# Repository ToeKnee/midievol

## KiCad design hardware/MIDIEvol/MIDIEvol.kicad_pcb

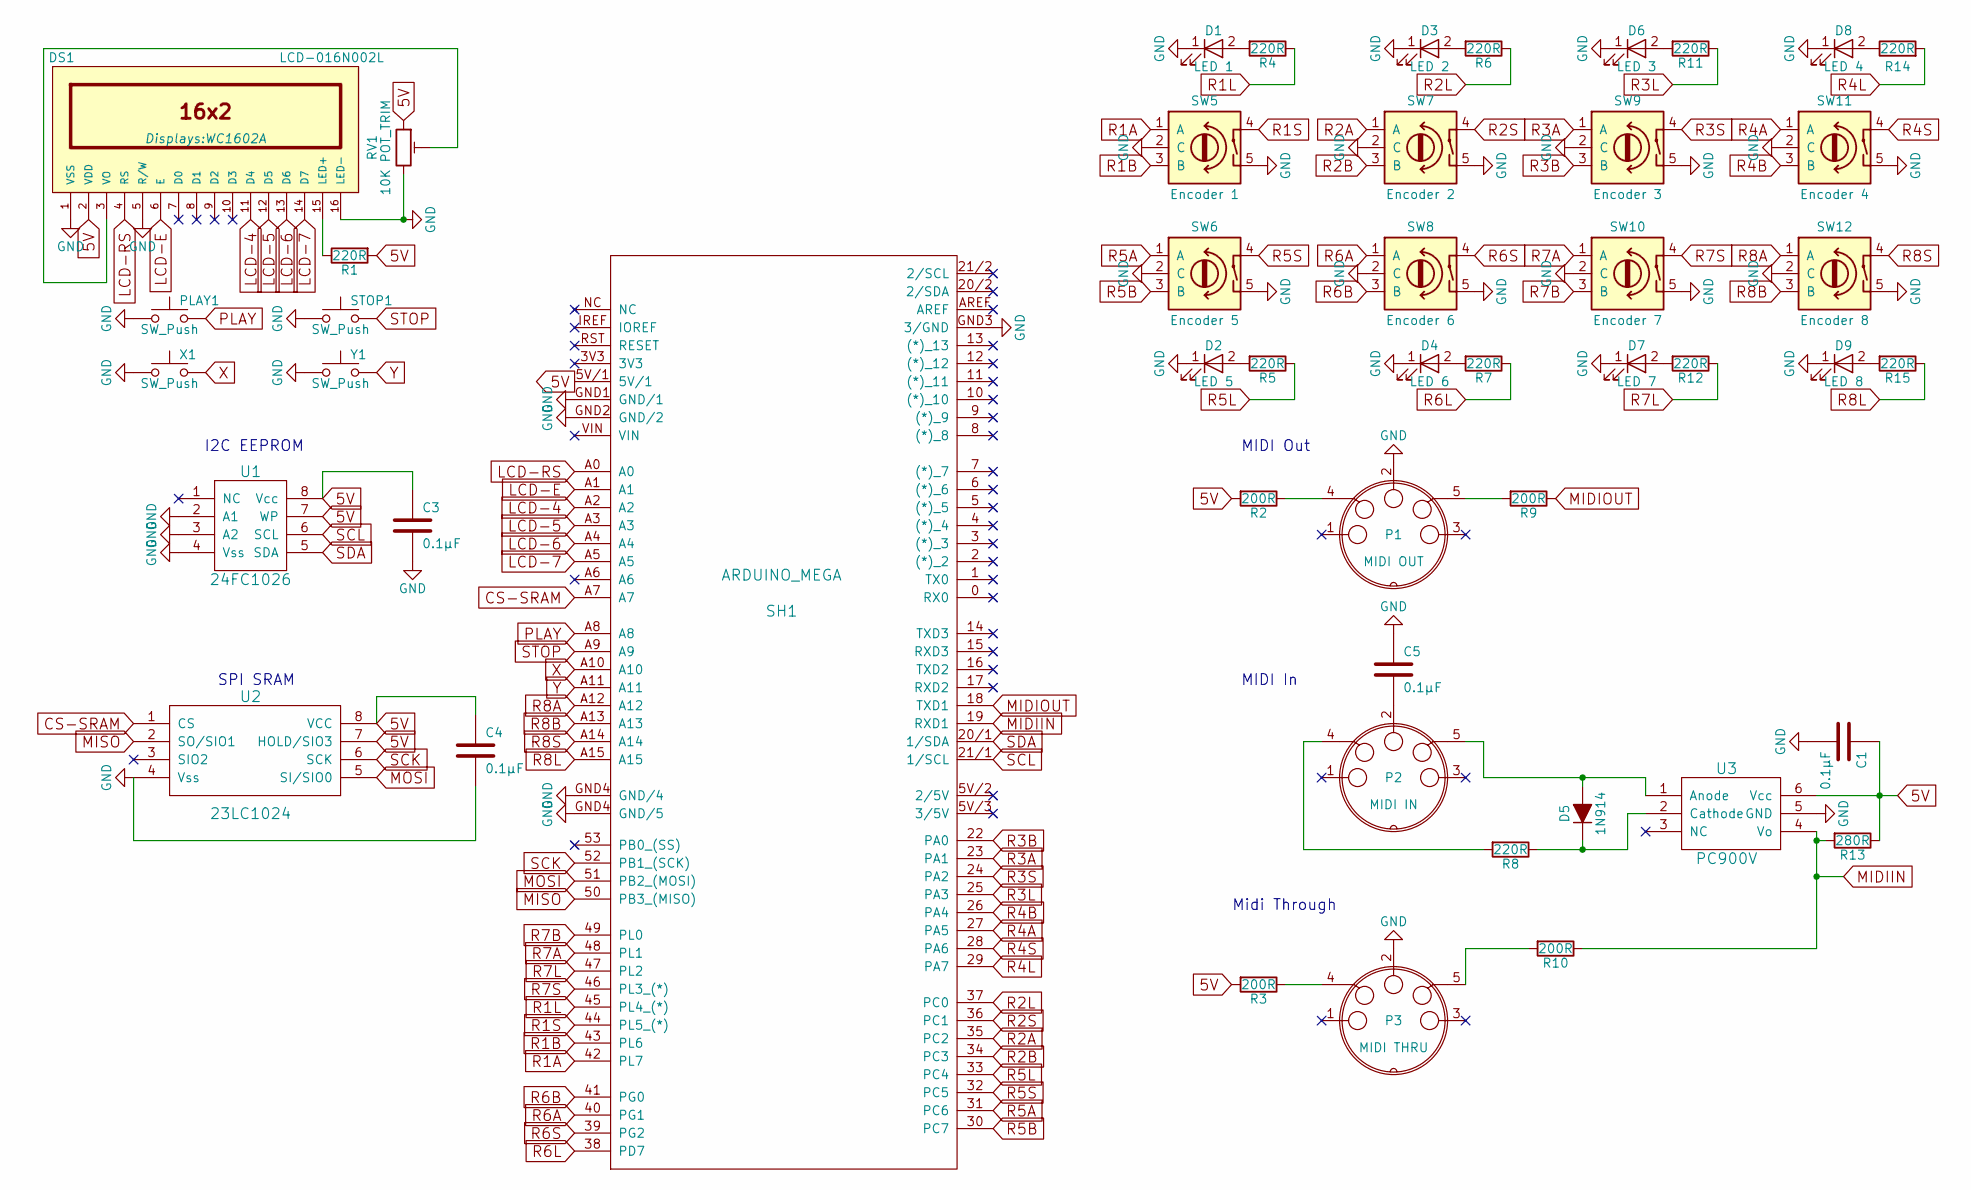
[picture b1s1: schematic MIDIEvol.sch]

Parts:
C1, C3, C4, C5: 0.1µF; C_Disc_D6_P5
D1: LED 1; LED-5MM
D2: LED 5; LED-5MM
D3: LED 2; LED-5MM
D4: LED 6; LED-5MM
D5: 1N914; D_DO-41_SOD81_P10.16mm_Horizontal
D6: LED 3; LED-5MM
D7: LED 7; LED-5MM
D8: LED 4; LED-5MM
D9: LED 8; LED-5MM
DS1: LCD-016N002L; WC1602A
P1: MIDI OUT; TerminalBlock_Pheonix_MPT-2.54mm_5pol
P2: MIDI IN; TerminalBlock_Pheonix_MPT-2.54mm_5pol
P3: MIDI THRU; TerminalBlock_Pheonix_MPT-2.54mm_5pol
PLAY1: SW_Push; CHERRY-MX1A-11NW_keyswitch
R1, R4, R5, R6, R7, R8, R11, R12, R14, R15: 220R; Resistor_Horizontal_RM10mm
R2, R3, R9, R10: 200R; Resistor_Horizontal_RM10mm
R13: 280R; Resistor_Horizontal_RM10mm
RV1: 10K POT_TRIM; Potentiometer_Trimmer-Suntan-TSR-3386P
SH1: ARDUINO_MEGA; ARDUINO_MEGA_2560_R3_CONTOUR
STOP1: SW_Push; CHERRY-MX1A-11NW_keyswitch
SW5: Encoder 1; AB2_ROTARY_ENCODER_W_SWITCH
SW6: Encoder 5; AB2_ROTARY_ENCODER_W_SWITCH
SW7: Encoder 2; AB2_ROTARY_ENCODER_W_SWITCH
SW8: Encoder 6; AB2_ROTARY_ENCODER_W_SWITCH
SW9: Encoder 3; AB2_ROTARY_ENCODER_W_SWITCH
SW10: Encoder 7; AB2_ROTARY_ENCODER_W_SWITCH
SW11: Encoder 4; AB2_ROTARY_ENCODER_W_SWITCH
SW12: Encoder 8; AB2_ROTARY_ENCODER_W_SWITCH
U1: 24FC1026; DIP-8_W7.62mm
U2: 23LC1024; DIP-8_W7.62mm
U3: PC900V; DIP-6_W7.62mm
X1: SW_Push; CHERRY-MX1A-11NW_keyswitch
Y1: SW_Push; CHERRY-MX1A-11NW_keyswitch

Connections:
5V: C1.1, C3.1, C4.1, DS1.2 (VDD), R1.2, R2.2, R3.2, R13.1, RV1.1, SH1.5V/1, U1.7 (WP), U1.8 (Vcc), U2.7 (HOLD/SIO3), U2.8 (VCC), U3.6 (Vcc)
CS-SRAM: SH1.A7, U2.1 (CS)
GND: C1.2, C3.2, C4.2, C5.1, D1.1 (K), D2.1 (K), D3.1 (K), D4.1 (K), D6.1 (K), D7.1 (K), D8.1 (K), D9.1 (K), DS1.1 (VSS), DS1.5 (R/W), DS1.16 (LED-), P1.2, P3.2, PLAY1.1, RV1.3, SH1.GND1 (GND/1), SH1.GND2 (GND/2), SH1.GND3 (3/GND), SH1.GND4 (GND/4), STOP1.1, SW5.2 (C), SW5.5, SW6.2 (C), SW6.5, SW7.2 (C), SW7.5, SW8.2 (C), SW8.5, SW9.2 (C), SW9.5, SW10.2 (C), SW10.5, SW11.2 (C), SW11.5, SW12.2 (C), SW12.5, U1.2 (A1), U1.3 (A2), U1.4 (Vss), U2.4 (Vss), U3.5 (GND), X1.1, Y1.1
LCD-4: DS1.11 (D4), SH1.A2
LCD-5: DS1.12 (D5), SH1.A3
LCD-6: DS1.13 (D6), SH1.A4
LCD-7: DS1.14 (D7), SH1.A5
LCD-E: DS1.6 (E), SH1.A1
LCD-RS: DS1.4 (RS), SH1.A0
MIDIIN: R10.1, R13.2, SH1.19 (RXD1), U3.4 (Vo)
MIDIOUT: R9.1, SH1.18 (TXD1)
MISO: SH1.50 (PB3_(MISO)), U2.2 (SO/SIO1)
MOSI: SH1.51 (PB2_(MOSI)), U2.5 (SI/SIO0)
unnamed: C5.2, P2.2
unnamed: D1.2 (A), R4.2
unnamed: D2.2 (A), R5.2
unnamed: D3.2 (A), R6.2
unnamed: D4.2 (A), R7.2
unnamed: D5.1 (K), R8.1, U3.2 (Cathode)
unnamed: D5.2 (A), P2.5, U3.1 (Anode)
unnamed: D6.2 (A), R11.2
unnamed: D7.2 (A), R12.2
unnamed: D8.2 (A), R14.1
unnamed: D9.2 (A), R15.2
unnamed: DS1.3 (VO), RV1.2
unnamed: DS1.15 (LED+), R1.1
unnamed: P1.4, R2.1
unnamed: P1.5, R9.2
unnamed: P2.4, R8.2
unnamed: P3.4, R3.1
unnamed: P3.5, R10.2
PLAY: PLAY1.2, SH1.A8
R1A: SH1.42 (PL7), SW5.1 (A)
R1B: SH1.43 (PL6), SW5.3 (B)
R1L: R4.1, SH1.45 (PL4_(*))
R1S: SH1.44 (PL5_(*)), SW5.4
R2A: SH1.35 (PC2), SW7.1 (A)
R2B: SH1.34 (PC3), SW7.3 (B)
R2L: R6.1, SH1.37 (PC0)
R2S: SH1.36 (PC1), SW7.4
R3A: SH1.23 (PA1), SW9.1 (A)
R3B: SH1.22 (PA0), SW9.3 (B)
R3L: R11.1, SH1.25 (PA3)
R3S: SH1.24 (PA2), SW9.4
R4A: SH1.27 (PA5), SW11.1 (A)
R4B: SH1.26 (PA4), SW11.3 (B)
R4L: R14.2, SH1.29 (PA7)
R4S: SH1.28 (PA6), SW11.4
R5A: SH1.31 (PC6), SW6.1 (A)
R5B: SH1.30 (PC7), SW6.3 (B)
R5L: R5.1, SH1.33 (PC4)
R5S: SH1.32 (PC5), SW6.4
R6A: SH1.40 (PG1), SW8.1 (A)
R6B: SH1.41 (PG0), SW8.3 (B)
R6L: R7.1, SH1.38 (PD7)
R6S: SH1.39 (PG2), SW8.4
R7A: SH1.48 (PL1), SW10.1 (A)
R7B: SH1.49 (PL0), SW10.3 (B)
R7L: R12.1, SH1.47 (PL2)
R7S: SH1.46 (PL3_(*)), SW10.4
R8A: SH1.A12, SW12.1 (A)
R8B: SH1.A13, SW12.3 (B)
R8L: R15.1, SH1.A15
R8S: SH1.A14, SW12.4
SCK: SH1.52 (PB1_(SCK)), U2.6 (SCK)
SCL: SH1.21/1 (1/SCL), U1.6 (SCL)
SDA: SH1.20/1 (1/SDA), U1.5 (SDA)
STOP: SH1.A9, STOP1.2
X: SH1.A10, X1.2
Y: SH1.A11, Y1.2

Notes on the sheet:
MIDI Out
MIDI In
Midi Through
I2C EEPROM
SPI SRAM

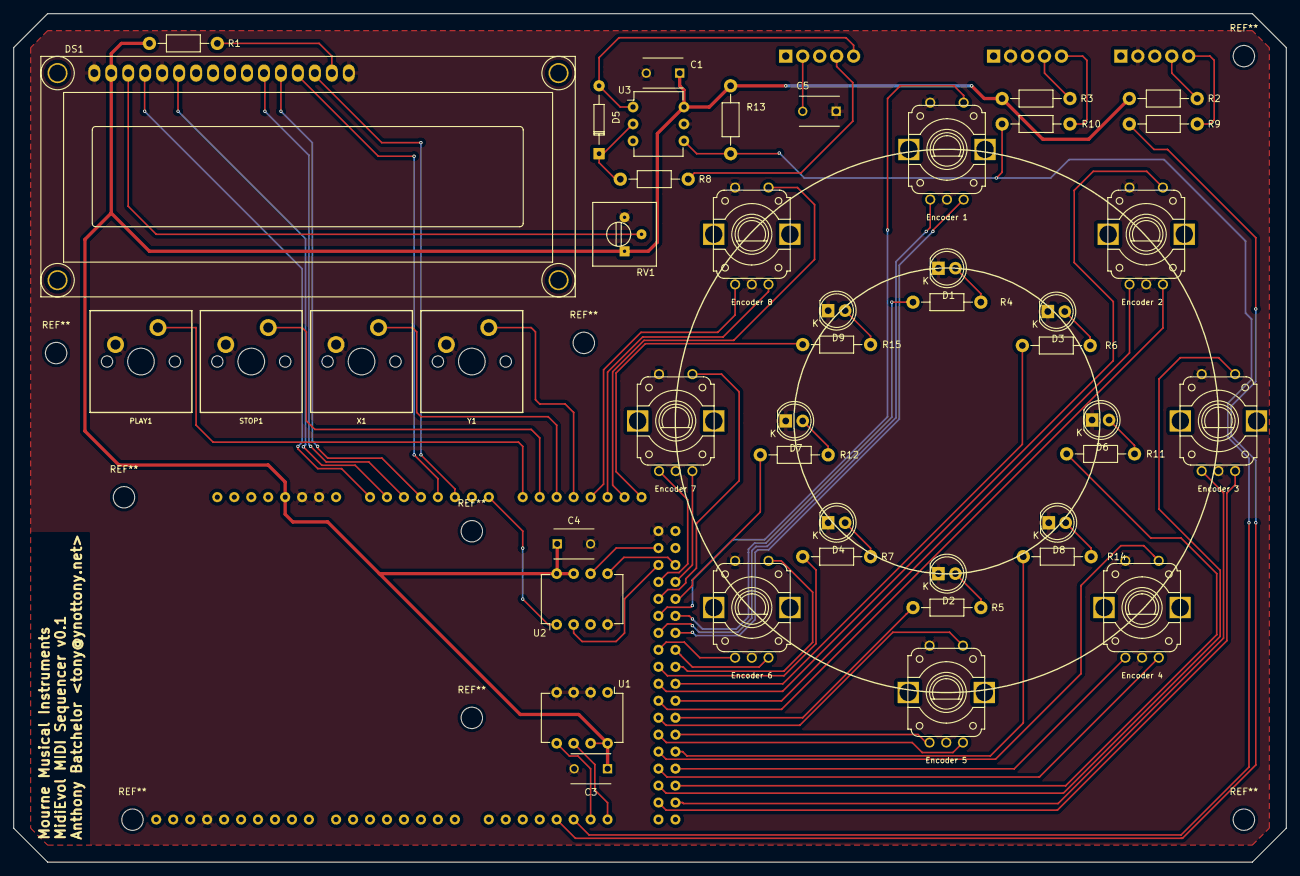
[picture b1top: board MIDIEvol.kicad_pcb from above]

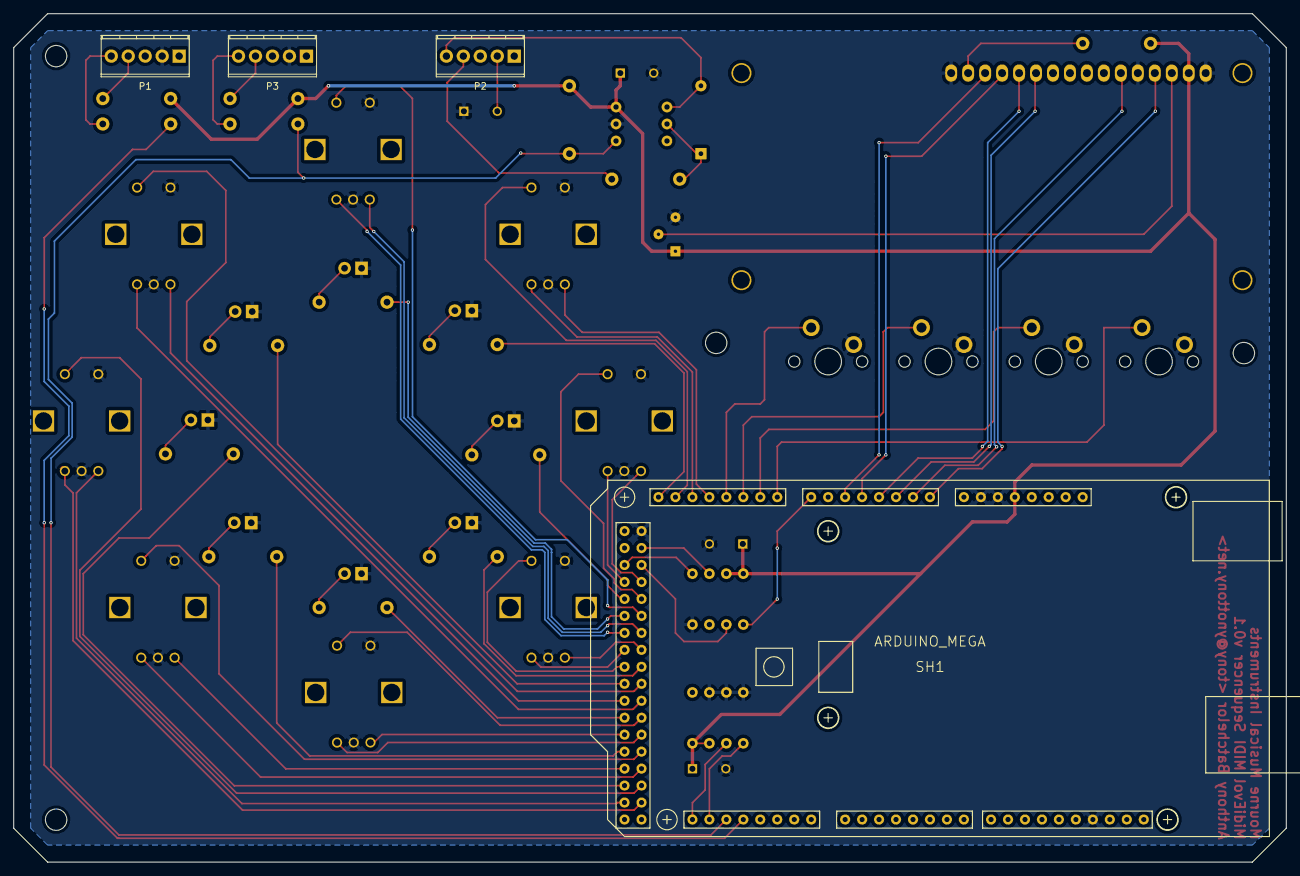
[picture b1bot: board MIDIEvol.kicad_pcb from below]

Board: 2 copper layers, 190.5 x 127.0 mm, 49 parts (4 on the bottom side), 70 nets.

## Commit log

2017-01-05 Add prototype for midi sequencer
2017-01-06 Improve handling of clock
2017-01-06 Update demo sequence
2017-01-06 Fix playing double notes
2017-01-09 Implement internal clock
2017-01-10 Add Play|Pause and Stop buttons
2017-01-10 Add hardware midi support on Serial1 (Arduino Mega2560)
    Remove support for hairless midi bridge
2017-01-17 Boot screen
2017-01-17 Remove debugging
2017-01-17 Improve Pause/Play handling
2017-01-17 Rotary Encoder support
    * Currently edits note[0]
2017-01-17 Change some default settings (legato, transpose)
2017-01-17 Handle Rest and Tie notes
2017-01-17 Display note names
2017-01-26 Implement handling of 4-step sequencer
    - Target is 64 on a 4 page 4 x 4 grid of Rotary Encoders
2017-01-26 Remove "Current Song Position" display
2017-01-26 Shift function - Handle BPM changes
2017-01-26 Display BPM < 10 correctly
2017-01-26 Change note displayed to either last edited or currently playing
2017-01-26 Remove debug Serial.println
2017-01-27 Add adjustable beat division
2017-01-28 Support the next 4 encoders (8-Step :))
2017-01-30 Implement note length support.
    * Remove old on/off triggering of notes
    * Add a kill list of notes and expiry times (allows many notes playing
    at once)
    * Rename reset_midi to panic
    * Don't call panic at stop/pause, just kill playing notes.
2017-01-30 Sequence length is now adjustable, up to 256 steps
2017-01-31 current_note can be a byte, not an int
2017-01-31 Fix tied notes
2017-01-31 No need to create a useless KillListNote
2017-01-31 Handle changing gate length
2017-01-31 Send appropriate midi messages
2017-02-01 Add Sequences data structure and lay foundation for load/save
2017-02-01 Split program into separate files
2017-02-01 Move some strings from global memory to program memory
2017-02-01 Ignore ~ files
2017-02-01 Move some more strings from global memory to program memory
2017-02-01 Use byte for bpm
2017-02-01 Use lcd.print instead of lcd.write
2017-02-02 Change settings to 16 channels of 64 steps
2017-02-02 Remove faulty temp code
2017-02-02 Starting point of Euclidean Drum sequencer
    All setup is random for now...
2017-02-03 Start on beat 0
    Was incrementing the beat before playing it, so starting on beat 2
2017-02-03 Change Drum pattern default to 1/16ths
2017-02-03 Drum patterns have to be at least 1 beat long
    Even if there are 0 beats
2017-02-03 Remove commented out code
2017-02-03 Handle rotation of Euclidean drum patterns
2017-02-03 Improve Drun interface
2017-02-03 Move files into src dir
2017-02-03 Move code to src/Evol/
2017-02-06 Improve Drum sequencing
    Can now edit beats, length, rotation and note
2017-02-06 Add AUTHORS file
2017-02-07 Fix beat counter
2017-02-08 Handle rotary encoders 8 - 11
2017-02-08 Initialise the sequencer nicely
2017-02-09 Load and Save sequences
2017-02-09 Fix midi channel
2017-02-10 Load and Save drum sequences
2017-02-12 Add encoders 12 - 15 for the 4 x 4 matrix
2017-02-13 Init drums to 16 beats in length
2017-02-13 Drums - Handle beats and length of pattern seperately
2017-02-13 Move timer handler into Evol
2017-02-14 Upcase enums
2017-02-15 Improve handling of status display
2017-02-15 Add Init Drum patterns
    Simple or Random for now
2017-02-16 Improve playing drum pattern display
2017-02-16 Drums: Rotate the patterns in the right direction
2017-02-16 Improve drum initialisation + new patterns
2017-02-17 Sequencer: Init sequences
2017-02-17 Drum: Refactor displaying of drum track status
2017-02-17 Drum: Rename edit enums
2017-02-17 Drum: Fix adjusting rotation length when going backwards
2017-02-17 Sequencer: Implement Note/Velocity/Note Length editing
2017-02-20 Sequencer: Set note length from sequences beat division
2017-02-20 Drum: Make Channel adjustable
2017-02-20 Sequencer: Make Channel adjustable
2017-02-20 Sequencer: Fix changing paramaters
2017-02-22 Change from parallel to I2C LCD interface
2017-02-22 Increase status timeout for drum patterns
2017-03-20 Change hardware to support only 8 channels
    16 channels was pushing the hardware a bit too much, I wasn't able to
    keep the latency low enough past 12 channels. Using only 8 should leave
    a fair bit of head room to implement other features.
2017-03-28 Initial hardware design
    Kicad files for Arduino Mega2560 based midi controller.
